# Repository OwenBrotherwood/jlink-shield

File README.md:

Bluz JLink Shield Hardware Files
==========
Bluz is a Development Kit (DK) that implements the Wiring language and talks to the [Particle](https://www.particle.io/) cloud through Bluetooth Low Energy. It can be accessed through a REST API and programmed from a Web IDE.

These files have been made available online through a [Creative Commons Attribution-ShareAlike 3.0](http://creativecommons.org/licenses/by-sa/3.0/) license.

You are welcome to distribute, remix, and use these files for commercial purposes. If you do so, please attribute the original design to Bluz both on the website and on the physical packaging of the product or in the instruction manual. All derivative works must be published under the same or a similar license.

All items are subject to change over time as the product is designed, so make sure you are always looking at the latest information by pulling often.

##Sections
<b>BOM</b>: Current Bill of Materials for the jlink shield.

<b>Datasheets</b>: Datasheets for all major parts on the board.

<b>HW Design</b>: Schematics, board layouts, and other design files.

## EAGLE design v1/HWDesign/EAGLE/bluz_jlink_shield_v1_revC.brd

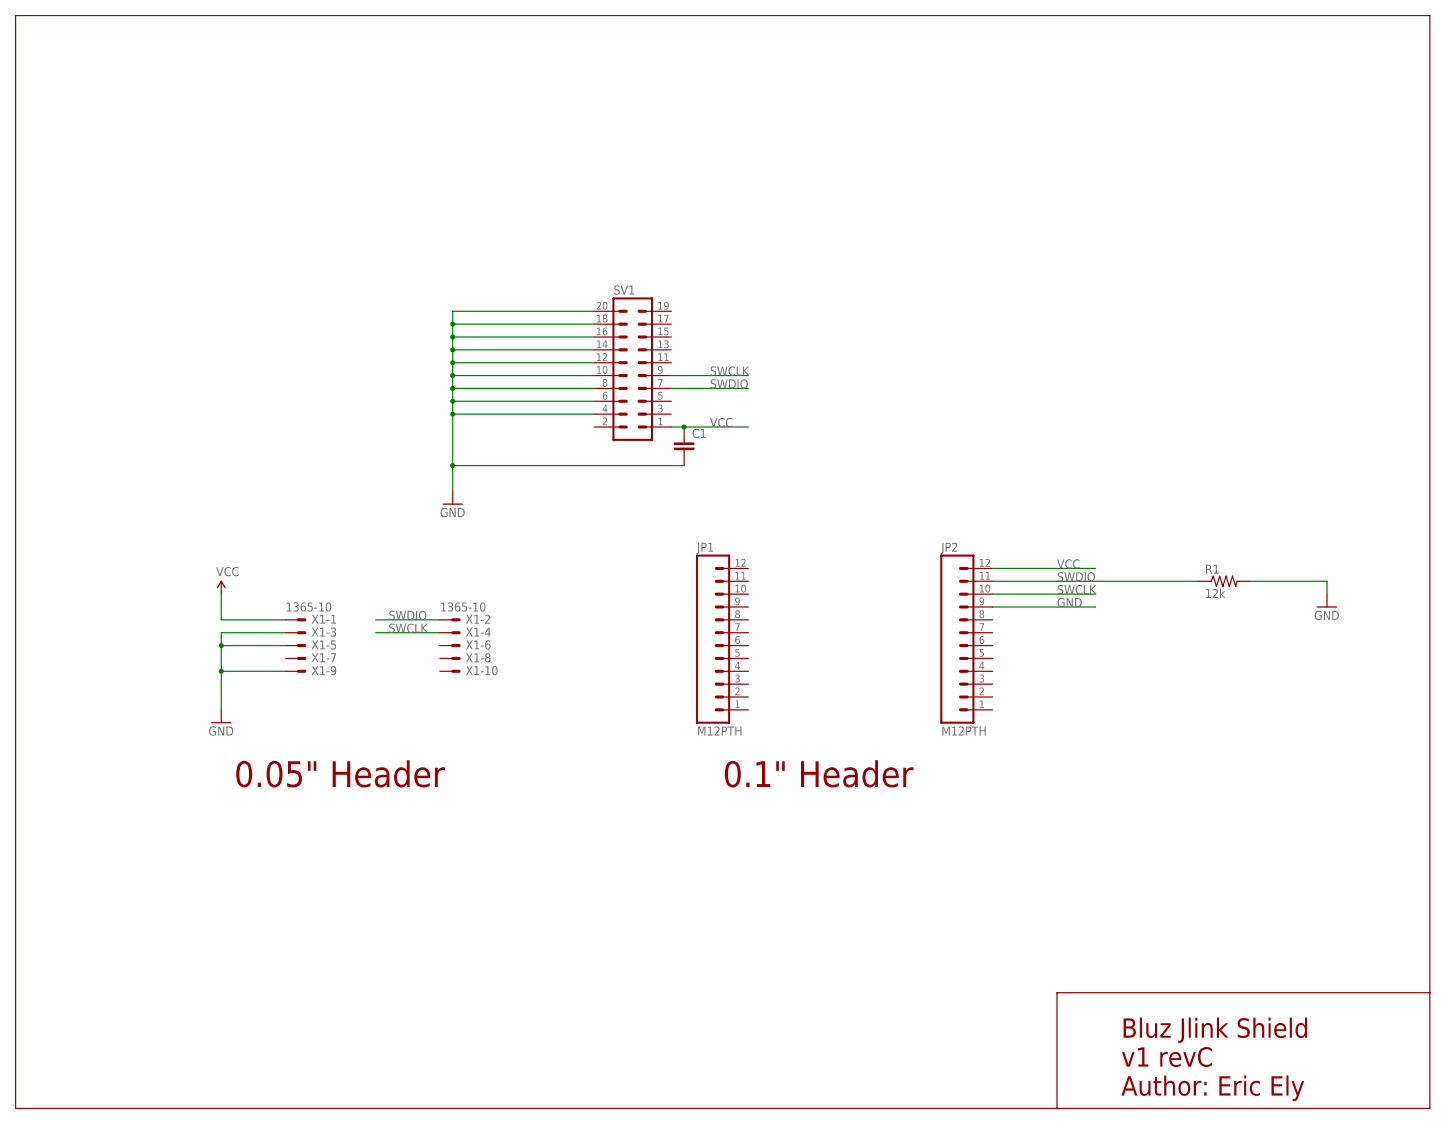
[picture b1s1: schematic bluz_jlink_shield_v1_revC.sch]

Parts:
C1: CAP0603-CAP; 0603-CAP
JP1, JP2: M12PTH; 1X12
R1: 12k; 0603-RES
SV1: ML20
X1: 1365-10

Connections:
GND: C1.2, JP2.9, R1.2, SV1.4, SV1.6, SV1.8, SV1.10, SV1.12, SV1.14, SV1.16, SV1.18, SV1.20, X1.3, X1.5, X1.9
SWCLK: JP2.10, SV1.9, X1.4
SWDIO: JP2.11, R1.1, SV1.7, X1.2
VCC: C1.1, JP2.12, SV1.1, X1.1

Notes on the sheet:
Bluz Jlink Shield v1 revC Author: Eric Ely
0.05" Header
0.1" Header

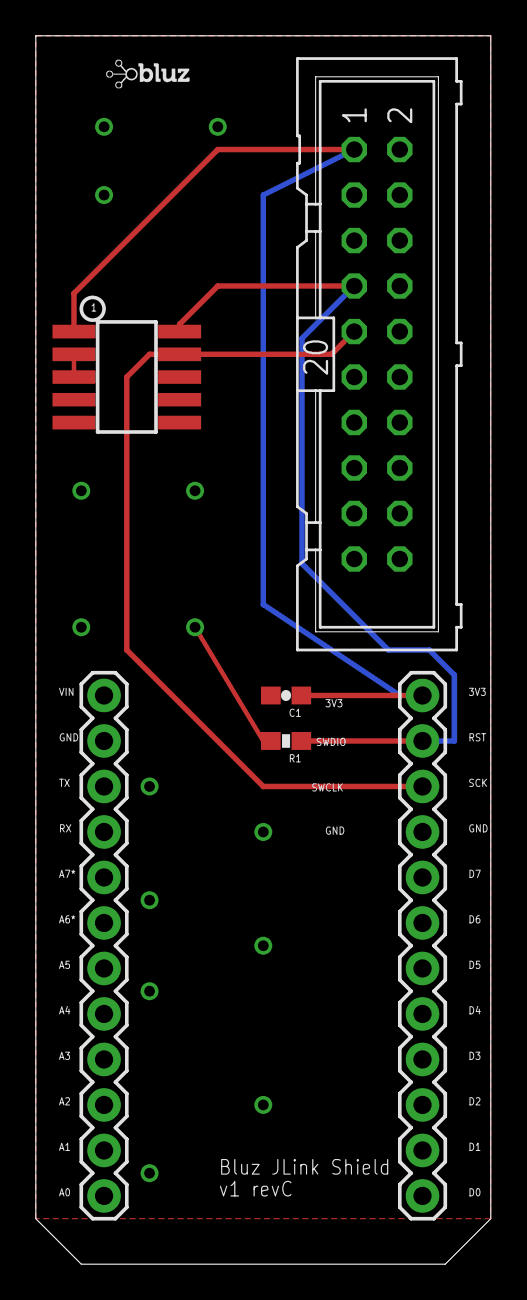
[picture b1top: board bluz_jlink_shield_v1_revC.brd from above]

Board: 2 copper layers, 25.4 x 68.6 mm, 7 parts (0 on the bottom side), 4 nets.

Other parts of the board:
U$1: BLUZE_LOGO_LOW_RES

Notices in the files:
parts and their libraries:
SparkFun-Connectors: Licensing: Creative Commons ShareAlike 4.0 International - https://creativecommons.org/licenses/by-sa/4.0
